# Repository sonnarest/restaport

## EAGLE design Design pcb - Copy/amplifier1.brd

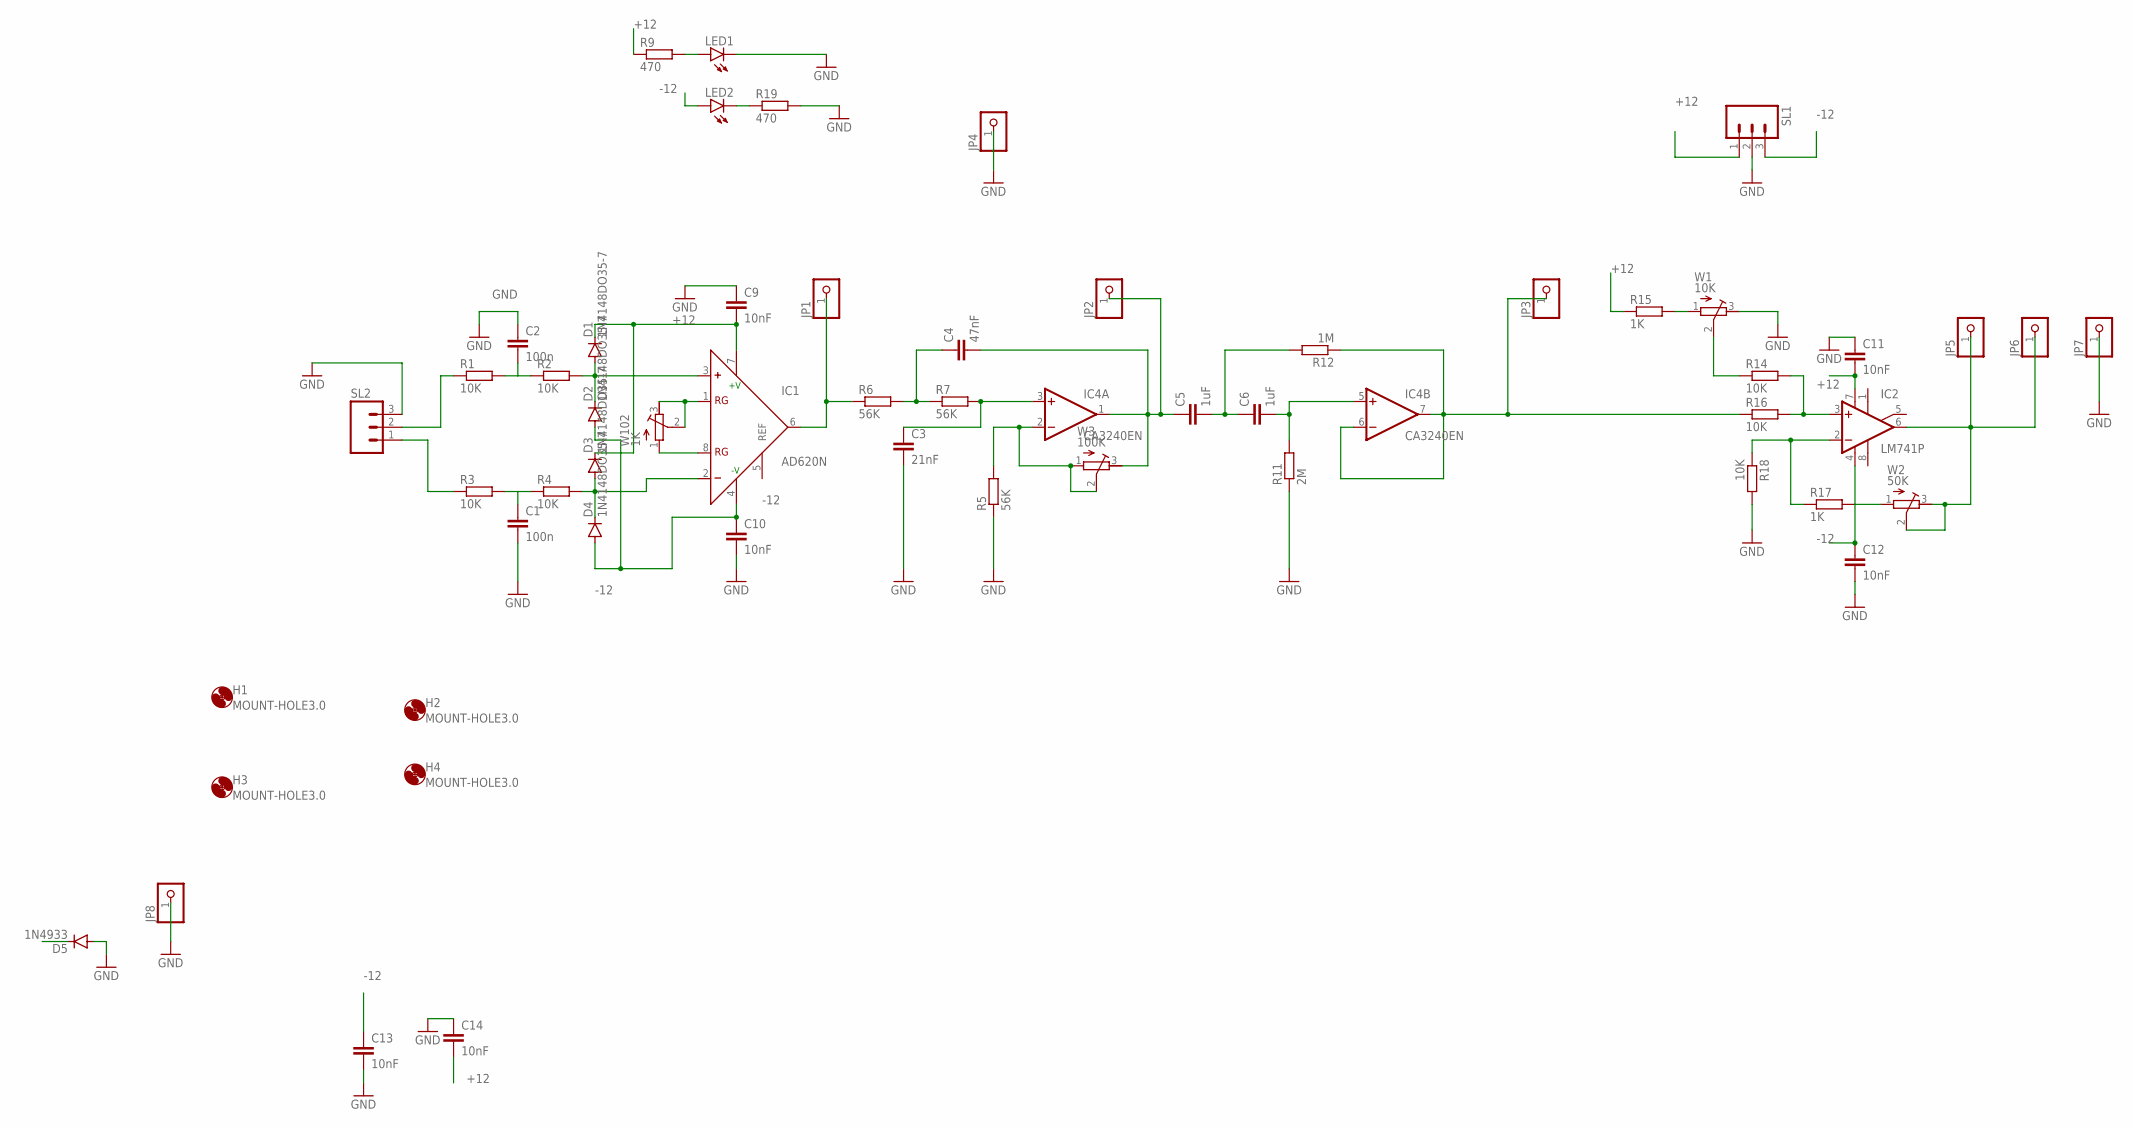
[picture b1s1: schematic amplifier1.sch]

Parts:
C1, C2: 100n; C025-025X050
C3: 21nF; C025-025X050
C4: 47nF; C025-025X050
C5, C6: 1uF; C025-025X050
C9, C10, C11, C12, C13, C14: 10nF; C025-040X050
D1, D2, D3, D4: 1N4148DO35-7; DO35-7
D5: 1N4933; DO41-10
H1, H2, H3, H4: MOUNT-HOLE3.0; 3,0
IC1: AD620N; DIL08
IC2: LM741P; DIL08
IC4: CA3240EN; DIL08
JP1, JP2, JP3, JP4, JP5, JP6, JP7, JP8: PINHD-1X1; 1X01
LED1, LED2: LED5MM
R1, R2, R3, R4: 10K; 0207/10
R5: 56K; 0204/7
R6, R7: 56K; 0207/10
R9, R19: 470; 0204/7
R11: 2M; 0207/10
R12: 1M; 0207/10
R14, R16, R18: 10K; 0204/7
R15, R17: 1K; 0204/7
SL1, SL2: M03; 03P
W1: 10K; RTRIM3299W
W2: 50K; RTRIM3299W
W3: 100K; RTRIM3299W
W102: 1K; RTRIM3299W

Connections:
+12: C9.2, C11.2, C14.2, D1.C, D3.C, IC1.7 (+V), IC2.7 (V+), IC4.8 (V+), R9.1, R15.1, SL1.1
-12: C10.1, C12.1, C13.1, D2.A, D4.A, IC1.4 (-V), IC2.4 (V-), IC4.4 (V-), LED2.A, SL1.3
GND: C1.2, C2.1, C3.2, C9.1, C10.2, C11.1, C12.2, C13.2, C14.1, D5.A, JP4.1, JP7.1, JP8.1, LED1.K (C), R5.1, R11.1, R18.2, R19.2, SL1.2, SL2.3, W1.3 (E)
unnamed: R1.1, SL2.2
unnamed: R3.1, SL2.1
unnamed: C1.1, R3.2, R4.1
unnamed: C2.2, R1.2, R2.1
unnamed: D1.A, D2.C, IC1.3 (+), R2.2
unnamed: D3.A, D4.C, IC1.2 (-), R4.2
unnamed: IC4.2 (-IN), R5.2, W3.1 (A), W3.2 (S)
unnamed: IC4.6 (-IN), IC4.7 (OUT), JP3.1, R12.1, R16.1
unnamed: IC1.8 (RG), W102.1 (A)
unnamed: IC1.1 (RG), W102.2 (S), W102.3 (E)
unnamed: IC1.6 (OUT), JP1.1, R6.1
unnamed: LED1.A, R9.2
unnamed: C5.2, C6.1, R12.2
unnamed: C4.1, R6.2, R7.1
unnamed: C4.2, C5.1, IC4.1 (OUT), JP2.1, W3.3 (E)
unnamed: C3.1, IC4.3 (+IN), R7.2
unnamed: C6.2, IC4.5 (+IN), R11.2
unnamed: LED2.K (C), R19.1
unnamed: R15.2, W1.1 (A)
unnamed: R14.1, W1.2 (S)
unnamed: IC2.3 (+IN), R14.2, R16.2
unnamed: IC2.2 (-IN), R17.1, R18.1
unnamed: IC2.6 (OUT), JP5.1, JP6.1, W2.2 (S), W2.3 (E)
unnamed: R17.2, W2.1 (A)

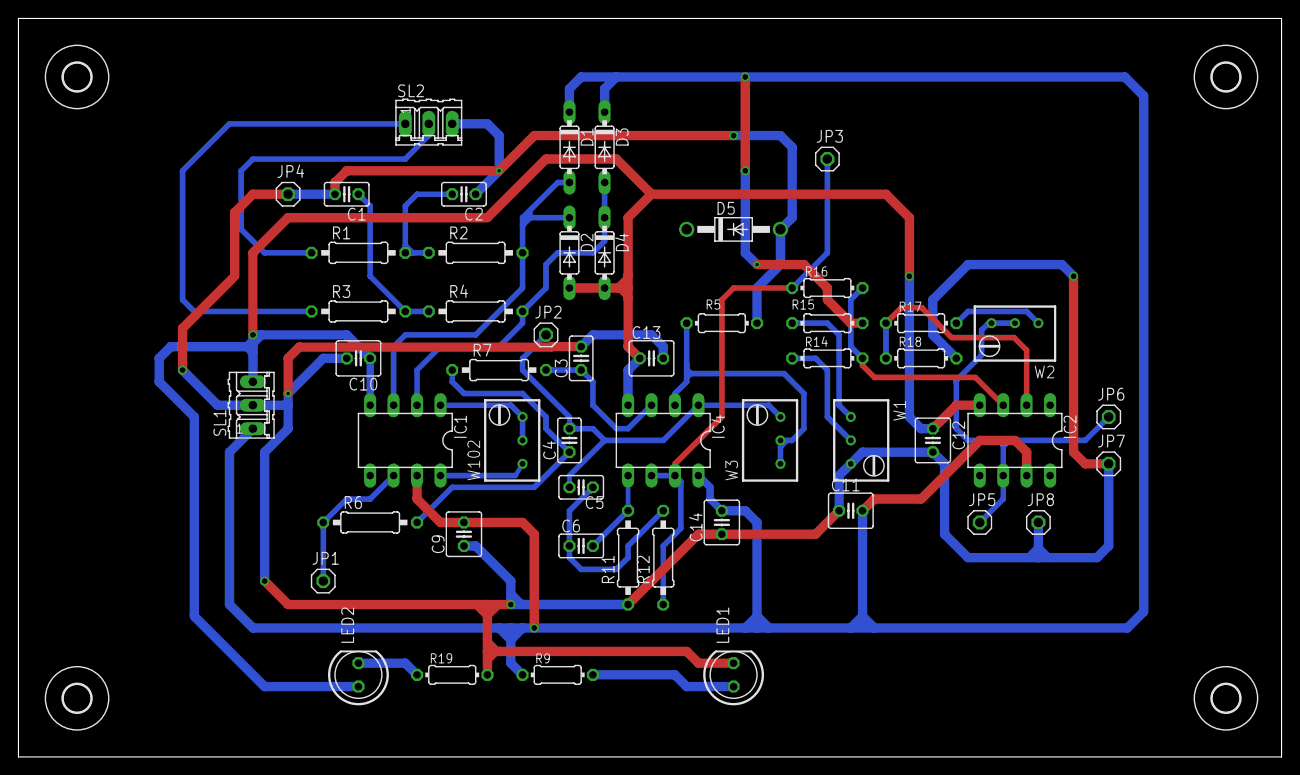
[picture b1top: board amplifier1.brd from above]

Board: 2 copper layers, 136.8 x 80.0 mm, 56 parts (0 on the bottom side), 27 nets.

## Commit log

2023-09-07 Create non-contact ECG
